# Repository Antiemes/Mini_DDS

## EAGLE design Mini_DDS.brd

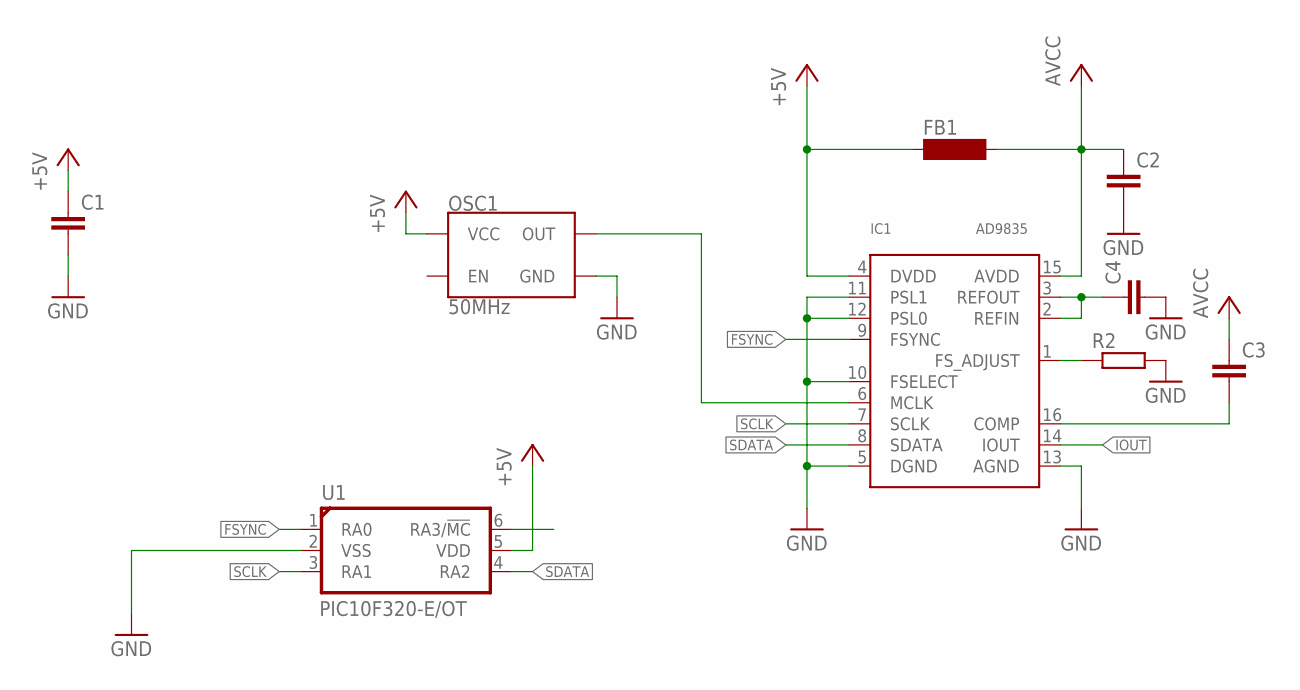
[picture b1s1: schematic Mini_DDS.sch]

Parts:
C1, C2, C3, C4: C-EUC0603K; C0603K
FB1: SM-1206
IC1: AD9835; TSSOP16
OSC1: 50MHz; OSCILLATOR-SMD-7X5-4PAD
R2: R-EU_R0603; R0603
U1: PIC10F320-E/OT; SOT23-6L

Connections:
+5V: C1.1, FB1.1, IC1.4 (DVDD), OSC1.4 (VCC), U1.5 (VDD)
FSYNC: IC1.9 (FSYNC), U1.1 (RA0)
GND: C1.2, C2.2, C4.2, IC1.5 (DGND), IC1.10 (FSELECT), IC1.11 (PSL1), IC1.12 (PSL0), IC1.13 (AGND), OSC1.2 (GND), R2.2, U1.2 (VSS)
IOUT: IC1.14 (IOUT)
unnamed: IC1.1 (FS_ADJUST), R2.1
unnamed: C3.2, IC1.16 (COMP)
unnamed: C4.1, IC1.2 (REFIN), IC1.3 (REFOUT)
unnamed: IC1.6 (MCLK), OSC1.3 (OUT)
SCLK: IC1.7 (SCLK), U1.3 (RA1)
SDATA: IC1.8 (SDATA), U1.4 (RA2)
VCC: C2.1, C3.1, FB1.2, IC1.15 (AVDD)

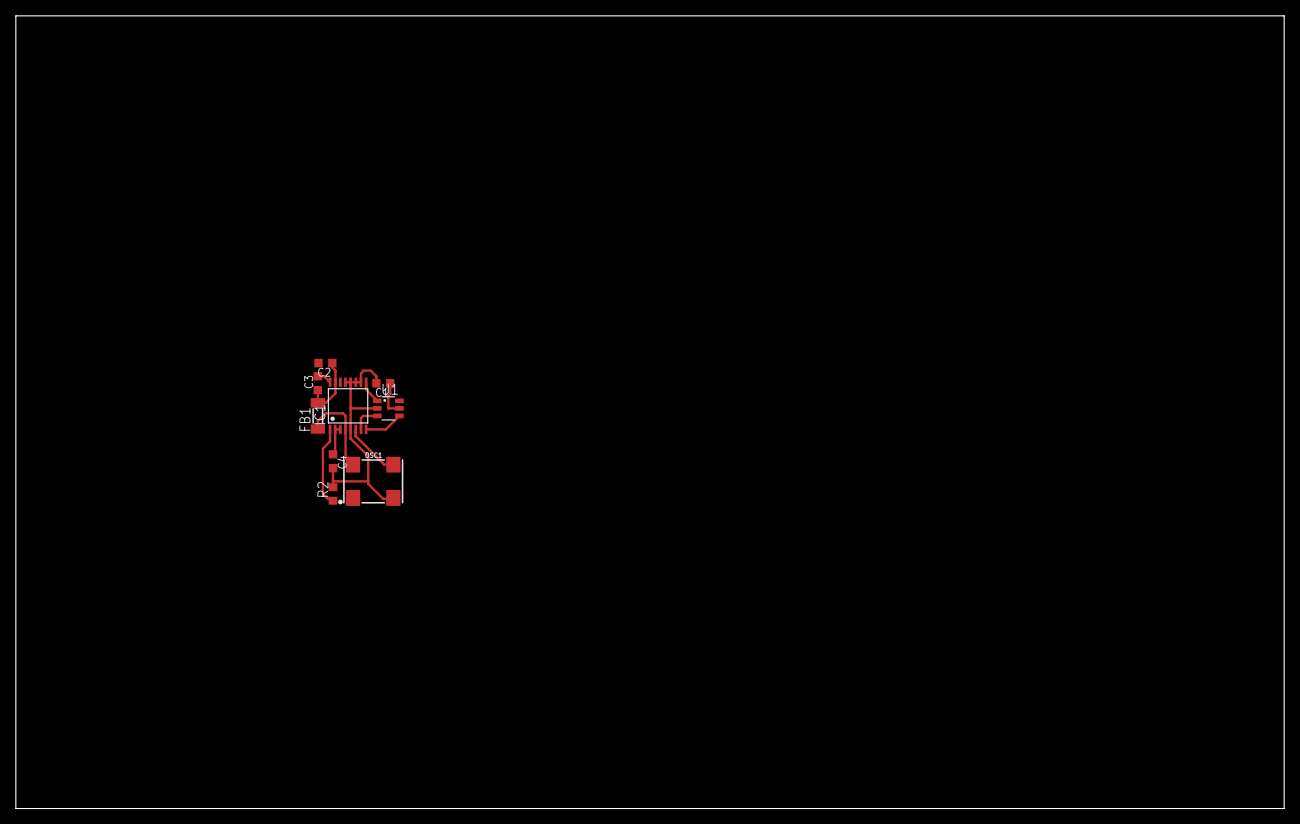
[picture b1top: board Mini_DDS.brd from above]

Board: 2 copper layers, 160.0 x 100.0 mm, 9 parts (0 on the bottom side), 10 nets.

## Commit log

2018-11-28 AD9834 and PIC10 libraries added
2018-12-03 Almost done

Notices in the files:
parts and their libraries:
SparkFun-Clocks: Licensing: Creative Commons ShareAlike 4.0 International - https://creativecommons.org/licenses/by-sa/4.0
